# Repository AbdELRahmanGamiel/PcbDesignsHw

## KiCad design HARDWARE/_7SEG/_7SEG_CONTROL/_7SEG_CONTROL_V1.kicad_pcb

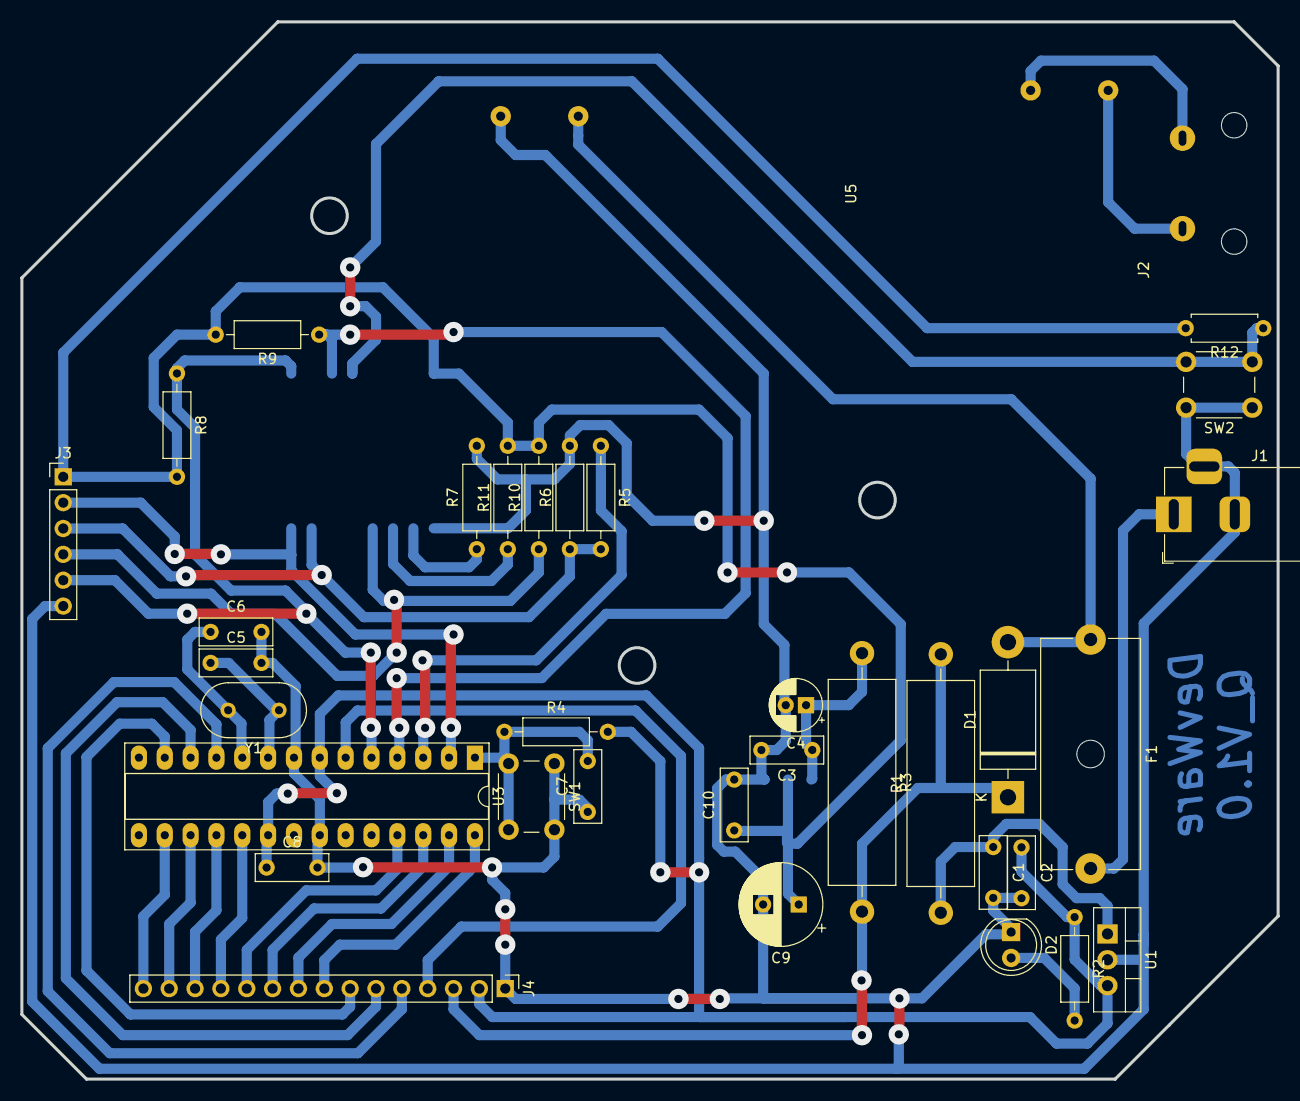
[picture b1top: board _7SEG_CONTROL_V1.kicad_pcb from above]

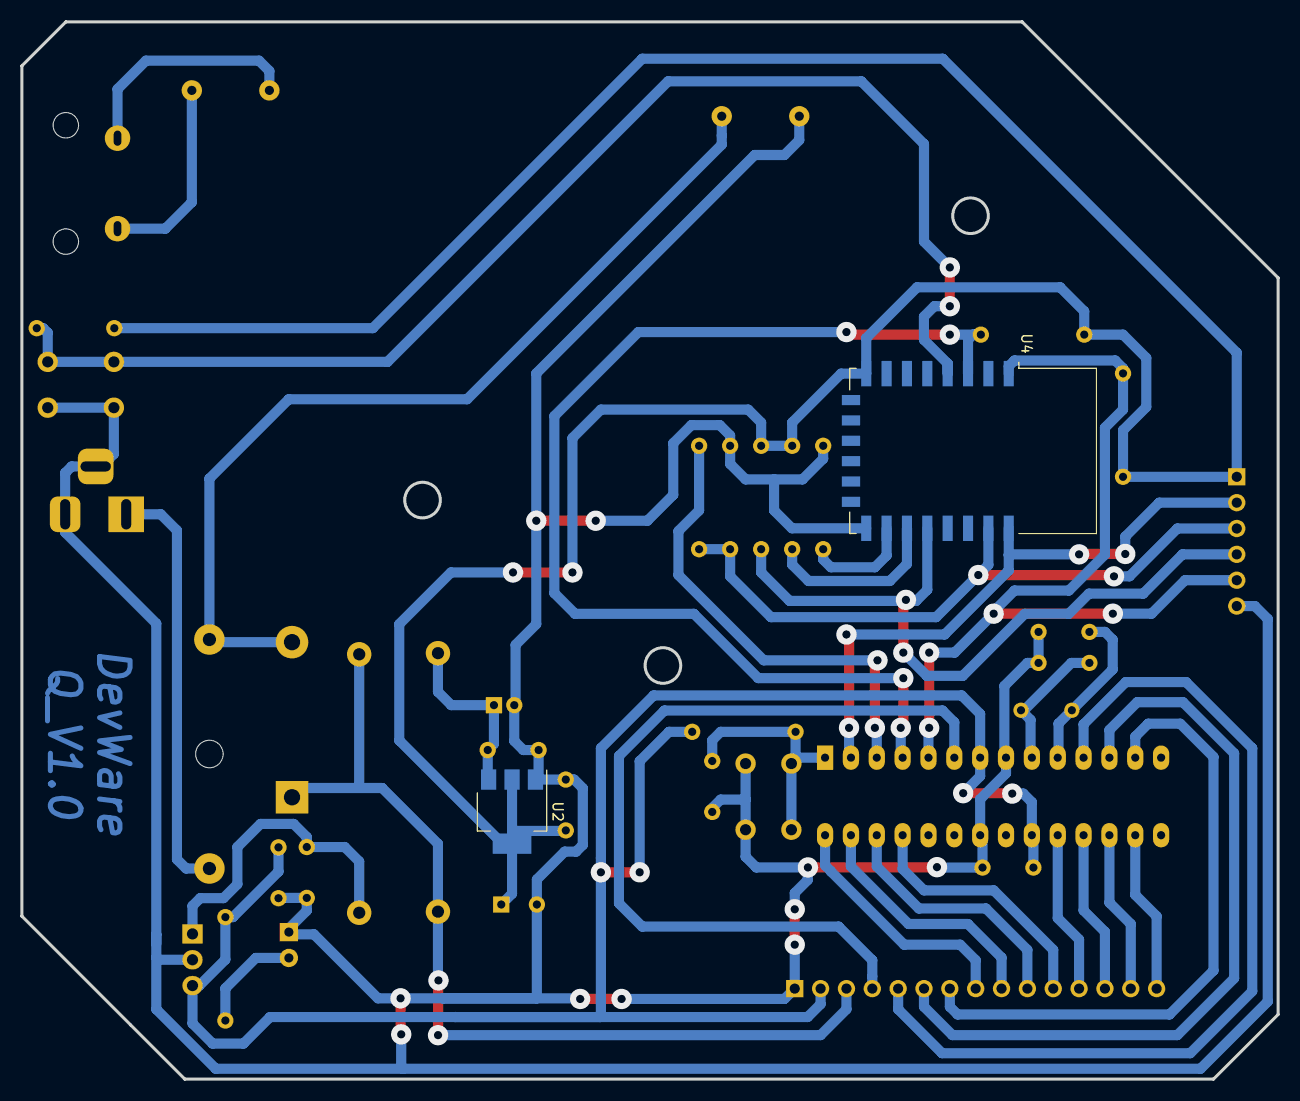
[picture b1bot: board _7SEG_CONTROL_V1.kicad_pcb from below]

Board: 2 copper layers, 123.4 x 103.9 mm, 37 parts (2 on the bottom side), 35 nets.

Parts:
C1, C3: 334; C_Disc_D7.0mm_W2.5mm_P5.00mm
C2, C7, C10: 104; C_Disc_D7.0mm_W2.5mm_P5.00mm
C4: 10UF; CP_Radial_D5.0mm_P2.00mm
C5, C6: 22P; C_Disc_D7.0mm_W2.5mm_P5.00mm
C8: 0.1UF; C_Disc_D7.0mm_W2.5mm_P5.00mm
C9: 100UF; CP_Radial_D8.0mm_P3.50mm
D1: 1N5407; D_DO-201AD_P15.24mm_Horizontal
D2: LED; LED_D5.0mm
F1: Fuse; Fuseholder_Cylinder-5x20mm_Schurter_0031_8201_Horizontal_Op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
J1: Barrel_Jack_Switch; BarrelJack_Horizontal
J2: AC_Socket
J3: CONFIG_ESP12; PinHeader_1x06_P2.54mm_Vertical
J4: Display_Board; PinHeader_1x15_P2.54mm_Vertical
R1: 10/2W; R_Axial_Power_L20.0mm_W6.4mm_P25.40mm
R2: 330; R_Axial_DIN0207_L6.3mm_D2.5mm_P10.16mm_Horizontal
R3: 10/3W; R_Axial_Power_L20.0mm_W6.4mm_P25.40mm
R4, R5, R6: 10K; R_Axial_DIN0207_L6.3mm_D2.5mm_P10.16mm_Horizontal
R7, R8, R9, R10, R11: 12K; R_Axial_DIN0207_L6.3mm_D2.5mm_P10.16mm_Horizontal
R12: 10K; R_Axial_DIN0207_L6.3mm_D2.5mm_P7.62mm_Horizontal
SW1, SW2: SW_Push; SW_PUSH_6mm_H7.3mm
U1: L7805; TO-220-3_Vertical
U2: AMS1117-3.3; SOT-223-3_TabPin2
U3: ATmega328-PU; DIP-28_W7.62mm_Socket_LongPads
U4: ESP-12E
U5: PS-12VDC; PS_12VDC
Y1: 16MH; Resonator-2Pin_W10.0mm_H5.0mm

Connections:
/3.3V: C9.1, C10.1, J3.1, R8.2, R9.2, R10.2, R11.2, R12.2, U2.2, U4.8
/5V: C2.1, C8.1, J4.2, R2.1, R4.2, U1.3, U3.7, U3.20
/12V: D1.1, J4.3, R1.2, R3.2
/A_D1: J4.15, U3.16
/A_D2: J4.11, U3.25
/A_D3: J4.7, U3.13
/B_D1: J4.12, U3.19
/B_D2: J4.8, U3.28
/B_D3: J4.4, U3.6
/C_D1: J4.13, U3.18
/C_D2: J4.9, U3.27
/C_D3: J4.5, U3.11
/D_D1: J4.14, U3.17
/D_D2: J4.10, U3.26
/D_D3: J4.6, U3.12
/EN: R9.1, U3.4, U4.3
/GND: C1.2, C2.2, C3.2, C4.2, C5.2, C6.2, C7.1, C8.2, C9.2, C10.2, D2.1, J1.2, J1.3, J3.6, J4.1, R6.2, R7.2, SW1.1, SW2.1, U1.2, U2.1, U3.8, U3.22, U4.15, U5.4
/IO0: J3.4, R10.1, U4.18
/IO2: R11.1, U4.17
/IO15: R7.1, U4.16
/Interrupt: R12.1, SW2.2, U4.4
/RST: J3.5, R8.1, U3.5, U4.1
/RX-MCU: J3.2, U3.2, U4.22
/RXD: J3.3, R5.2, R6.1, U4.21
/TX_MCU: R5.1, U3.3
/V+: D1.2, F1.1, U5.3
unnamed: C1.1, R1.1, U1.1
unnamed: C3.1, C4.1, R3.1, U2.3
unnamed: C5.1, U3.9, Y1.1
unnamed: C6.1, U3.10, Y1.2
unnamed: C7.2, R4.1, SW1.2, U3.1
unnamed: D2.2, R2.2
unnamed: F1.2, J1.1
unnamed: J2.L, U5.1
unnamed: J2.N, U5.2

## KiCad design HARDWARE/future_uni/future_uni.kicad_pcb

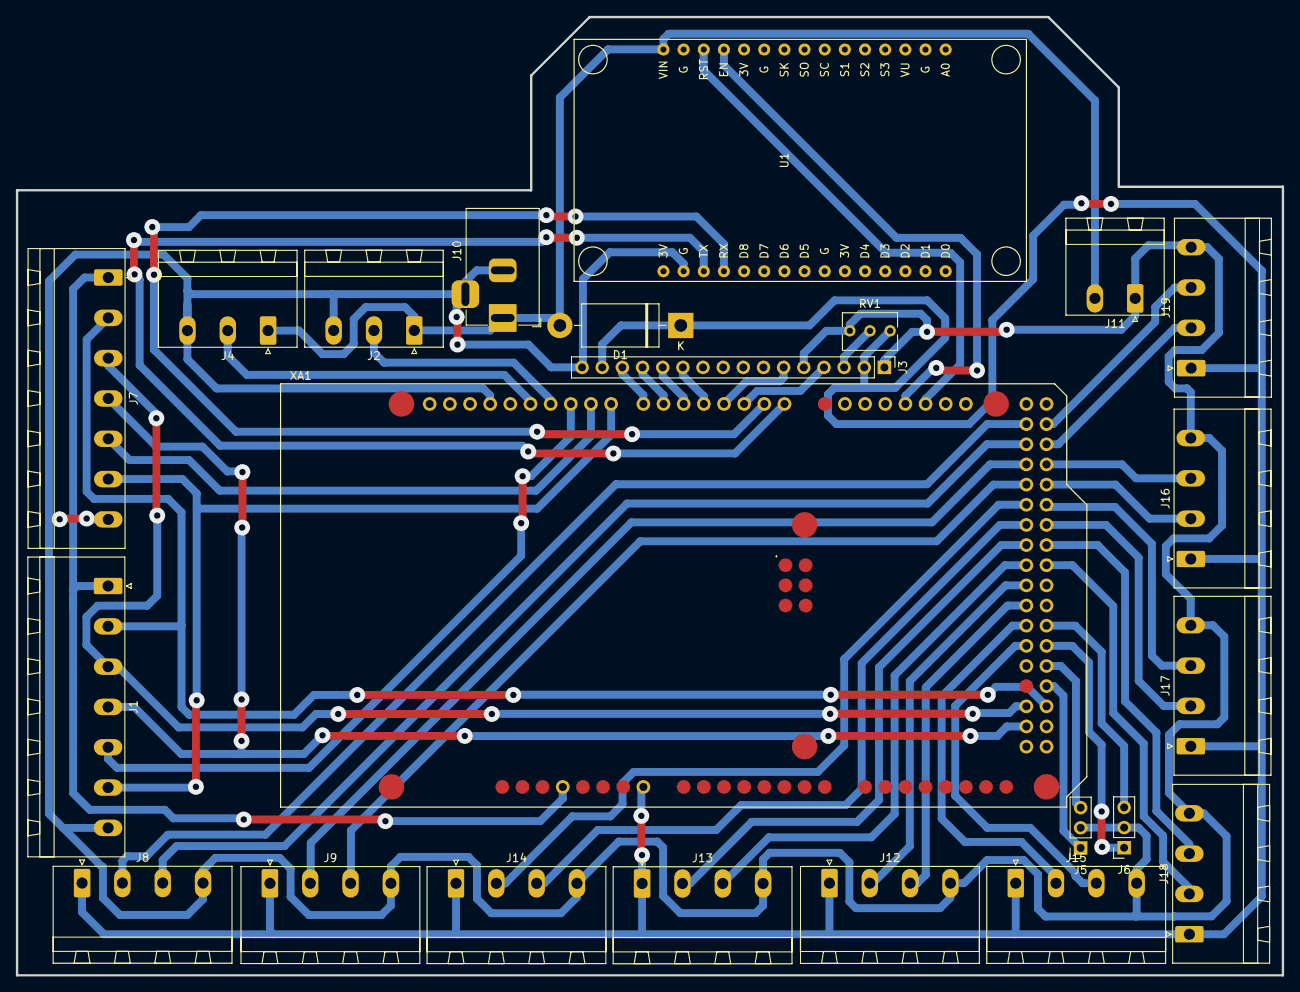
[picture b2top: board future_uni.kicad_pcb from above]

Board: 2 copper layers, 159.5 x 120.8 mm, 23 parts (0 on the bottom side), 47 nets.

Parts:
D1: D; D_DO-201AD_P15.24mm_Horizontal
J1: RFID_2; PhoenixContact_MSTBA_2,5_7-G-5,08_1x07_P5.08mm_Horizontal
J2: Servo_1; PhoenixContact_MSTBA_2,5_3-G-5,08_1x03_P5.08mm_Horizontal
J3: LCD (2*16); PinHeader_1x16_P2.54mm_Vertical
J4: Servo_2; PhoenixContact_MSTBA_2,5_3-G-5,08_1x03_P5.08mm_Horizontal
J5: RGB_1; PinSocket_1x03_P2.54mm_Vertical
J6: RGB_2; PinSocket_1x03_P2.54mm_Vertical
J7: RFID_1; PhoenixContact_MSTBA_2,5_7-G-5,08_1x07_P5.08mm_Horizontal
J8: Ultra_10; PhoenixContact_MSTBA_2,5_4-G-5,08_1x04_P5.08mm_Horizontal
J9: Ultra_9; PhoenixContact_MSTBA_2,5_4-G-5,08_1x04_P5.08mm_Horizontal
J10: 5V_PWR; BarrelJack_Horizontal
J11: 5V_PWR; PhoenixContact_MSTBA_2,5_2-G-5,08_1x02_P5.08mm_Horizontal
J12: Ultra_6; PhoenixContact_MSTBA_2,5_4-G-5,08_1x04_P5.08mm_Horizontal
J13: Ultra_7; PhoenixContact_MSTBA_2,5_4-G-5,08_1x04_P5.08mm_Horizontal
J14: Ultra_8; PhoenixContact_MSTBA_2,5_4-G-5,08_1x04_P5.08mm_Horizontal
J15: Ultra_5; PhoenixContact_MSTBA_2,5_4-G-5,08_1x04_P5.08mm_Horizontal
J16: Ultra_2; PhoenixContact_MSTBA_2,5_4-G-5,08_1x04_P5.08mm_Horizontal
J17: Ultra_3; PhoenixContact_MSTBA_2,5_4-G-5,08_1x04_P5.08mm_Horizontal
J18: Ultra_4; PhoenixContact_MSTBA_2,5_4-G-5,08_1x04_P5.08mm_Horizontal
J19: Ultra_1; PhoenixContact_MSTBA_2,5_4-G-5,08_1x04_P5.08mm_Horizontal
RV1: R_POT; Potentiometer_Bourns_3266Y_Vertical
U1: NodeMCU1.0(ESP-12E); NodeMCU-LoLinV3
XA1: Arduino_Mega2560_Shield

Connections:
/3.3V: J1.1, J7.1, XA1.3V3
/5V: D1.1, J3.2, J3.15, J8.1, J9.1, J12.1, J13.1, J14.1, J15.1, J16.1, J17.1, J18.1, J19.1, RV1.1, XA1.VIN
/DB4: J3.11, XA1.D4
/DB5: J3.12, XA1.D5
/DB6: J3.13, XA1.D6
/DB7: J3.14, XA1.D7
/E: J3.6, XA1.D3
/ECHO_1: J19.3, XA1.D23
/ECHO_2: J16.3, XA1.D27
/ECHO_3: J17.3, XA1.D31
/ECHO_4: J18.3, XA1.D35
/ECHO_5: J15.3, XA1.D44
/ECHO_6: J12.3, XA1.D40
/ECHO_7: J13.3, XA1.D36
/ECHO_8: J14.3, XA1.D32
/ECHO_9: J9.3, XA1.D28
/ECHO_10: J8.3, XA1.D24
/EN_ESP: U1.12, XA1.D18
/GND: J1.7, J2.3, J3.1, J3.5, J3.16, J4.3, J5.2, J6.2, J7.7, J8.4, J9.4, J10.2, J10.3, J11.1, J12.4, J13.4, J14.4, J15.4, J16.4, J17.4, J18.4, J19.4, RV1.3, U1.17, XA1.GND1
/GREEN_1: J5.3, XA1.D47
/GREEN_2: J6.3, XA1.D43
/MISO: J1.3, J7.3, XA1.D50
/MOSI: J1.2, J7.2, XA1.D51
/RED_1: J5.1, XA1.D49
/RED_2: J6.1, XA1.D45
/RS: J3.4, XA1.D2
/RST: J1.6, J7.6, XA1.D8
/RST_ESP: U1.13, XA1.D19
/RX_MCU: U1.18, XA1.D0
/SCK: J1.4, J7.4, XA1.D52
/SDA\SS_1: J7.5, XA1.D9
/SDA\SS_2: J1.5, XA1.D10
/Signal_1: J2.2, XA1.D11
/Signal_2: J4.2, XA1.D12
/TRIG_1: J19.2, XA1.D25
/TRIG_2: J16.2, XA1.D29
/TRIG_3: J17.2, XA1.D33
/TRIG_4: J18.2, XA1.D37
/TRIG_5: J15.2, XA1.D42
/TRIG_6: J12.2, XA1.D38
/TRIG_7: J13.2, XA1.D34
/TRIG_8: J14.2, XA1.D30
/TRIG_9: J9.2, XA1.D26
/TRIG_10: J8.2, XA1.D22
/TX_MCU: U1.19, XA1.D1
/VIN: D1.2, J2.1, J4.1, J10.1, J11.2, U1.15
/VO: J3.3, RV1.2

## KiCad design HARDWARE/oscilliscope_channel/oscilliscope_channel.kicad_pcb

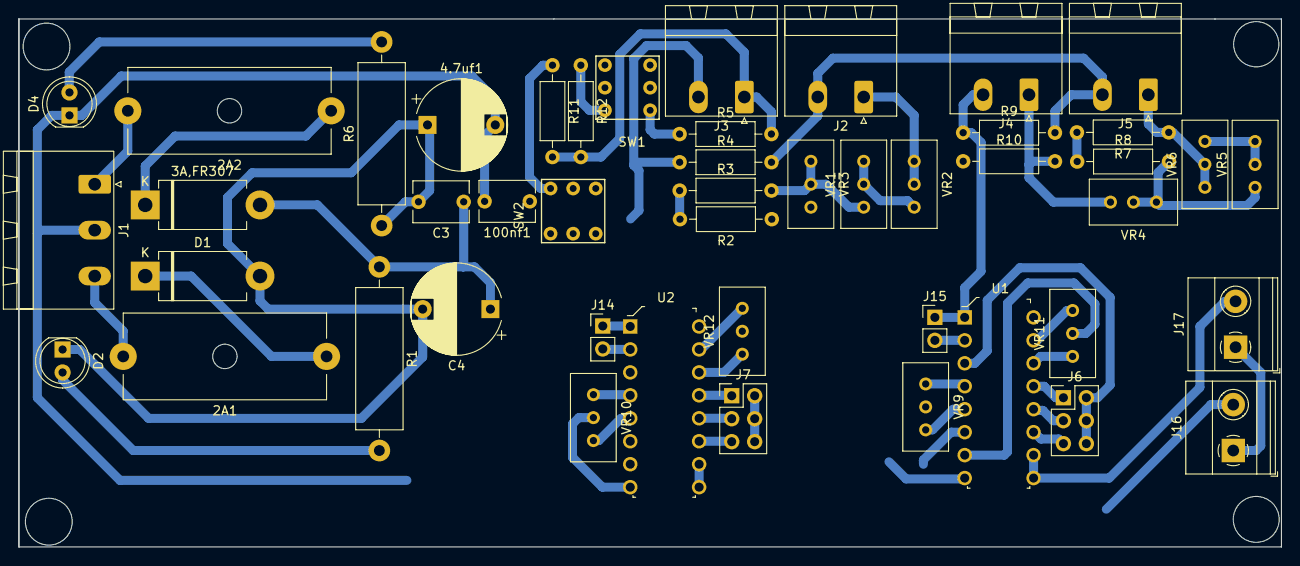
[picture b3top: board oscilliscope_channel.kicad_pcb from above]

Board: 2 copper layers, 139.7 x 58.4 mm, 47 parts (0 on the bottom side), 40 nets.

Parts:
2A1, 2A2: Fuse; Fuseholder_Cylinder-5x20mm_Schurter_0031_8201_Horizontal_Op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
3A,FR307: DIODE; D_DO-201AD_P12.70mm_Horizontal
4.7uf1: CP; CP_Radial_D10.0mm_P7.50mm
100nf1: C; C_Disc_D6.0mm_W4.4mm_P5.00mm
C3: 100nf; C_Disc_D6.0mm_W4.4mm_P5.00mm
C4: 4.7uf,25v; CP_Radial_D10.0mm_P7.50mm
D1: 3A,FR307; D_DO-201AD_P12.70mm_Horizontal
D2, D4: LED; LED_D5.0mm
J1: Screw_Terminal_01x03; PhoenixContact_MSTBA_2,5_3-G-5,08_1x03_P5.08mm_Horizontal
J2, J3, J4, J5: Screw_Terminal_01x02; PhoenixContact_MSTBA_2,5_2-G-5,08_1x02_P5.08mm_Horizontal
J6, J7: Conn_02x03_Counter_Clockwise; PinHeader_2x03_P2.54mm_Vertical
J14, J15: Conn_01x02_Male; PinHeader_1x02_P2.54mm_Vertical
J16, J17: Screw_Terminal_01x02; TerminalBlock_Phoenix_MKDS-1,5-2-5.08_1x02_P5.08mm_Horizont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
R1: 910OHM,1W; R_Axial_DIN0516_L15.5mm_D5.0mm_P20.32mm_Horizontal
R2, R7: 10kohm; R_Axial_DIN0207_L6.3mm_D2.5mm_P10.16mm_Horizontal
R3, R8: 1kohm; R_Axial_DIN0207_L6.3mm_D2.5mm_P10.16mm_Horizontal
R4, R9: 120ohm; R_Axial_DIN0207_L6.3mm_D2.5mm_P10.16mm_Horizontal
R5, R10: 150ohm; R_Axial_DIN0207_L6.3mm_D2.5mm_P10.16mm_Horizontal
R6: 910ohm,1W; R_Axial_DIN0516_L15.5mm_D5.0mm_P20.32mm_Horizontal
R11, R12: 20kohm; R_Axial_DIN0207_L6.3mm_D2.5mm_P10.16mm_Horizontal
SW1, SW2: SW_DIP_x03
U1, U2: AD524BDZ; DIP-16_W7.62mm
VR1, VR5: 1KOHM; Potentiometer_Bourns_3296W_Vertical
VR2, VR6: 5KOHM; Potentiometer_Bourns_3296W_Vertical
VR3, VR4: 500OHM; Potentiometer_Bourns_3296W_Vertical
VR9, VR10, VR11, VR12: 10KOHM; Potentiometer_Bourns_3296W_Vertical

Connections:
/5V: J3.1, J4.1, R5.2, R10.2, R11.2, R12.2, VR3.1, VR4.1
/15V: 3A,FR307.2, C3.1, C4.1, R1.1, U1.8, U2.8, VR9.2, VR10.2
/-15V: 4.7uf1.2, 100nf1.2, D4.1, J1.2, U1.7, U2.7, VR11.2, VR12.2
/G10-1: J7.1, U2.13
/G10-2: J6.1, U1.13
/G100-1: J7.3, U2.12
/G100-2: J6.3, U1.12
/G1000-1: J7.5, U2.11
/G1000-2: J6.5, U1.11
/GND: 4.7uf1.1, 100nf1.1, C3.2, C4.2, D1.2, D2.1, J2.2, J5.2, J16.1, J17.1, R4.2, R6.1, R9.2, U1.6, U2.6
/OUT1: J16.2, U2.9, U2.10
/OUT-2: J17.2, U1.9, U1.10
/P1-1: J3.2, J14.1, R4.1, U2.1
/P1-2: J2.1, J14.2, R2.1, R5.1, SW1.1, U2.2, VR2.2, VR2.3
/P2-1: J4.2, J15.1, R9.1, U1.1
/P2-2: J5.1, J15.2, R7.1, R10.1, SW2.1, U1.2, VR6.2, VR6.3
/RG2-1: J7.2, J7.4, J7.6, U2.3
/RG2-2: J6.2, J6.4, J6.6, U1.3
unnamed: 2A1.1, D1.1
unnamed: 2A1.2, J1.3
unnamed: 2A2.1, 3A,FR307.1
unnamed: 2A2.2, J1.1
unnamed: D2.2, R1.2
unnamed: D4.2, R6.2
unnamed: R2.2, R3.1
unnamed: R3.2, VR1.3, VR3.2, VR3.3
unnamed: R7.2, R8.1
unnamed: R8.2, VR4.2, VR4.3, VR5.3
unnamed: R11.1, SW2.2
unnamed: R12.1, SW1.2
unnamed: U1.4, VR9.3
unnamed: U1.5, VR9.1
unnamed: U1.14, VR11.3
unnamed: U1.15, VR11.1
unnamed: U2.4, VR10.3
unnamed: U2.5, VR10.1
unnamed: U2.14, VR12.3
unnamed: U2.15, VR12.1
unnamed: VR1.1, VR1.2, VR2.1
unnamed: VR5.1, VR5.2, VR6.1

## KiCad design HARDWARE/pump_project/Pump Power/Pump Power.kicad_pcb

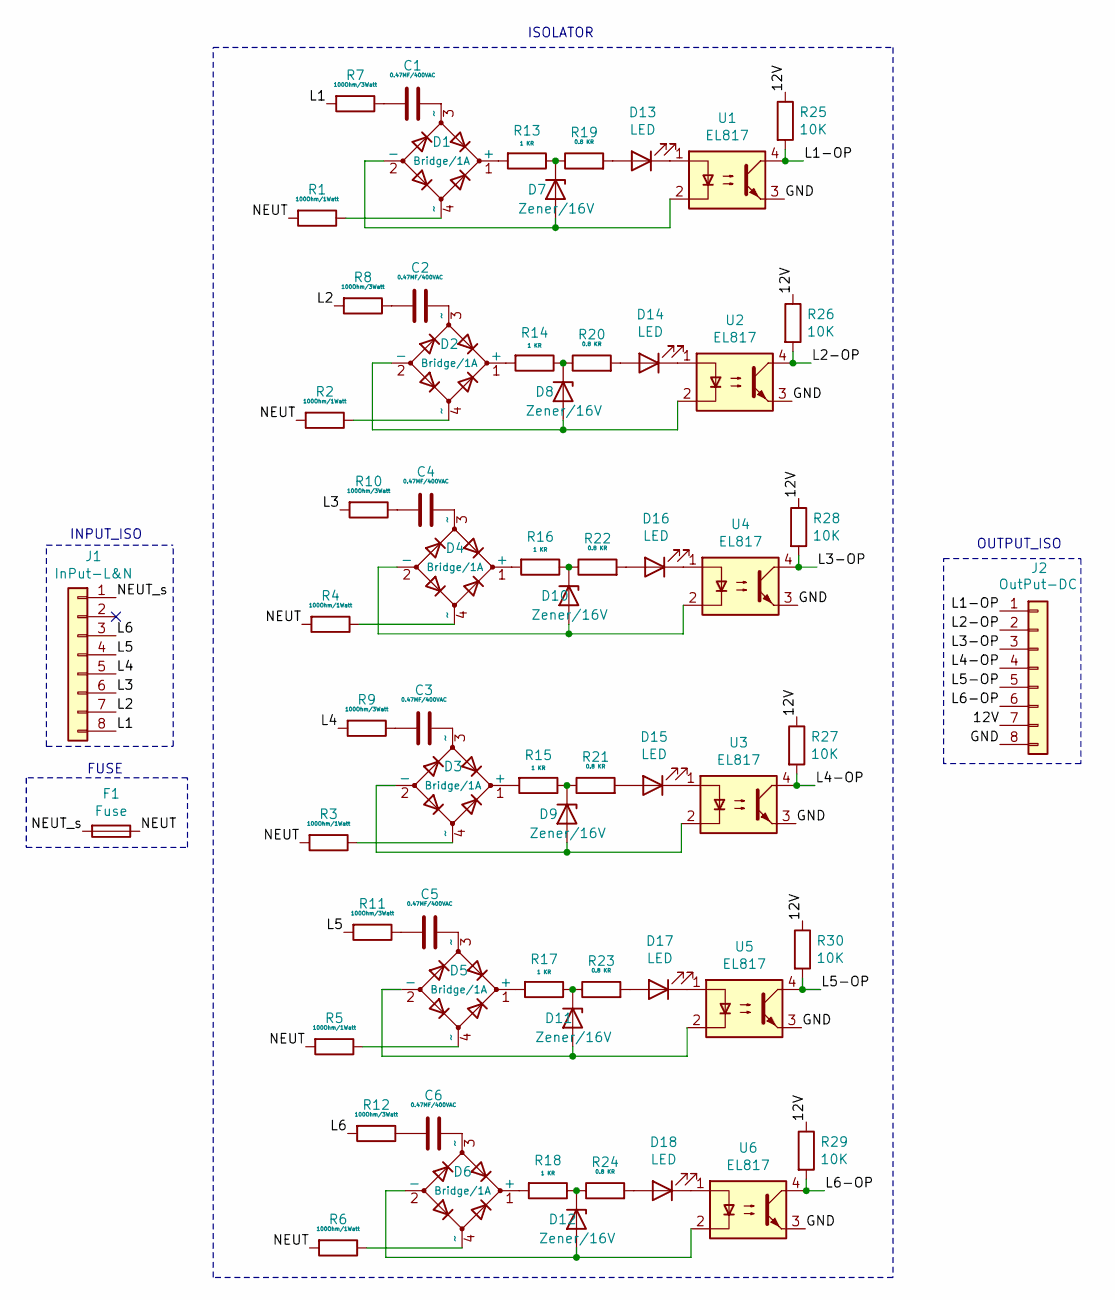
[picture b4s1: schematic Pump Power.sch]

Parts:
C1, C2, C3, C4, C5, C6: 0.47MF/400VAC; C_Rect_L11.5mm_W5.6mm_P10.00mm_MKT
D1, D2, D3, D4, D5, D6: Bridge/1A; Diode_Bridge_Round_D9.8mm
D7, D8, D9, D10, D11, D12: Zener/16V; D_A-405_P7.62mm_Horizontal
D13, D14, D15, D16, D17, D18: LED; LED_D5.0mm
F1: Fuse; Fuseholder_Cylinder-6.3x32mm_Schurter_0031-8002_Horizontal_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
J1: InPut-L&N; PhoenixContact_MSTBA_2,5_8-G-5,08_1x08_P5.08mm_Horizontal
J2: OutPut-DC; PhoenixContact_MSTBA_2,5_8-G-5,08_1x08_P5.08mm_Horizontal
R1, R2, R3, R4, R5, R6: 100Ohm/1Watt; R_Axial_DIN0617_L17.0mm_D6.0mm_P20.32mm_Horizontal
R7, R8, R9, R10, R11, R12: 100Ohm/3Watt; R_Axial_Power_L25.0mm_W9.0mm_P27.94mm
R13, R14, R15, R16, R17, R18: 1 KR; R_Axial_DIN0207_L6.3mm_D2.5mm_P10.16mm_Horizontal
R19, R20, R21, R22, R23, R24: 0.8 KR; R_Axial_DIN0207_L6.3mm_D2.5mm_P10.16mm_Horizontal
R25, R26, R27, R28, R29, R30: 10K; R_Axial_DIN0207_L6.3mm_D2.5mm_P10.16mm_Horizontal
U1, U2, U3, U4, U5, U6: EL817; DIP-4_W7.62mm

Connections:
/12V: J2.7, R25.1, R26.1, R27.1, R28.1, R29.1, R30.1
/GND: J2.8, U1.3, U2.3, U3.3, U4.3, U5.3, U6.3
/L1: J1.8, R7.2
/L1-OP: J2.1, R25.2, U1.4
/L2: J1.7, R8.2
/L2-OP: J2.2, R26.2, U2.4
/L3: J1.6, R10.2
/L3-OP: J2.3, R28.2, U4.4
/L4: J1.5, R9.2
/L4-OP: J2.4, R27.2, U3.4
/L5: J1.4, R11.2
/L5-OP: J2.5, R30.2, U5.4
/L6: J1.3, R12.2
/L6-OP: J2.6, R29.2, U6.4
/NEUT: F1.1, R1.2, R2.2, R3.2, R4.2, R5.2, R6.2
/NEUT_s: F1.2, J1.1
unnamed: C1.1, D1.3 (~~)
unnamed: C1.2, R7.1
unnamed: C2.1, D2.3 (~~)
unnamed: C2.2, R8.1
unnamed: C3.1, D3.3 (~~)
unnamed: C3.2, R9.1
unnamed: C4.1, D4.3 (~~)
unnamed: C4.2, R10.1
unnamed: C5.1, D5.3 (~~)
unnamed: C5.2, R11.1
unnamed: C6.1, D6.3 (~~)
unnamed: C6.2, R12.1
unnamed: D1.1 (+), R13.2
unnamed: D1.2 (-), D7.2 (A), U1.2
unnamed: D1.4 (~~), R1.1
unnamed: D2.1 (+), R14.2
unnamed: D2.2 (-), D8.2 (A), U2.2
unnamed: D2.4 (~~), R2.1
unnamed: D3.1 (+), R15.2
unnamed: D3.2 (-), D9.2 (A), U3.2
unnamed: D3.4 (~~), R3.1
unnamed: D4.1 (+), R16.2
unnamed: D4.4 (~~), R4.1
unnamed: D5.1 (+), R17.2
unnamed: D5.4 (~~), R5.1
unnamed: D6.1 (+), R18.2
unnamed: D6.4 (~~), R6.1
unnamed: D7.1 (K), R13.1, R19.1
unnamed: D8.1 (K), R14.1, R20.1
unnamed: D9.1 (K), R15.1, R21.1
unnamed: D10.1 (K), R16.1, R22.1
unnamed: D4.2 (-), D10.2 (A), U4.2
unnamed: D11.1 (K), R17.1, R23.1
unnamed: D5.2 (-), D11.2 (A), U5.2
unnamed: D12.1 (K), R18.1, R24.1
unnamed: D6.2 (-), D12.2 (A), U6.2
unnamed: D13.1 (K), U1.1
unnamed: D13.2 (A), R19.2
unnamed: D14.1 (K), U2.1
unnamed: D14.2 (A), R20.2
unnamed: D15.1 (K), U3.1
unnamed: D15.2 (A), R21.2
unnamed: D16.1 (K), U4.1
unnamed: D16.2 (A), R22.2
unnamed: D17.1 (K), U5.1
unnamed: D17.2 (A), R23.2
unnamed: D18.1 (K), U6.1
unnamed: D18.2 (A), R24.2

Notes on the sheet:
ISOLATOR
INPUT_ISO
OUTPUT_ISO
FUSE

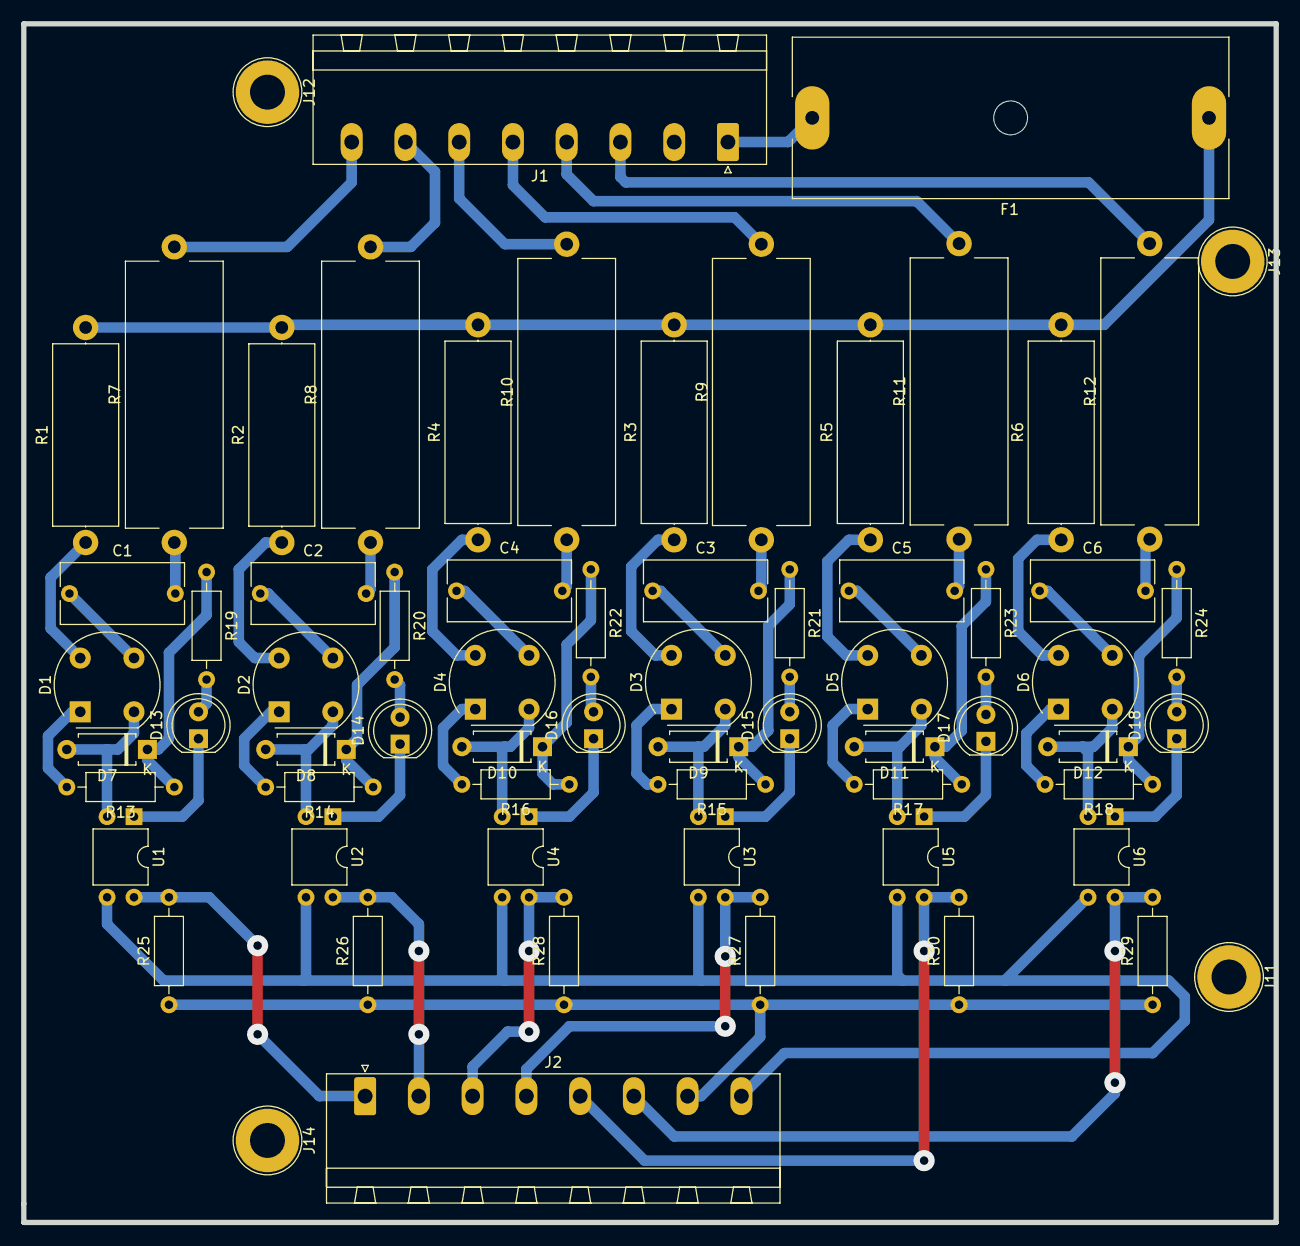
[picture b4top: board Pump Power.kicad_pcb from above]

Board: 2 copper layers, 118.4 x 113.3 mm, 67 parts (0 on the bottom side), 64 nets.

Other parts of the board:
J11, J12, J13, J14: Screw_Terminal_01x01; TestPoint_Plated_Hole_D5.0mm

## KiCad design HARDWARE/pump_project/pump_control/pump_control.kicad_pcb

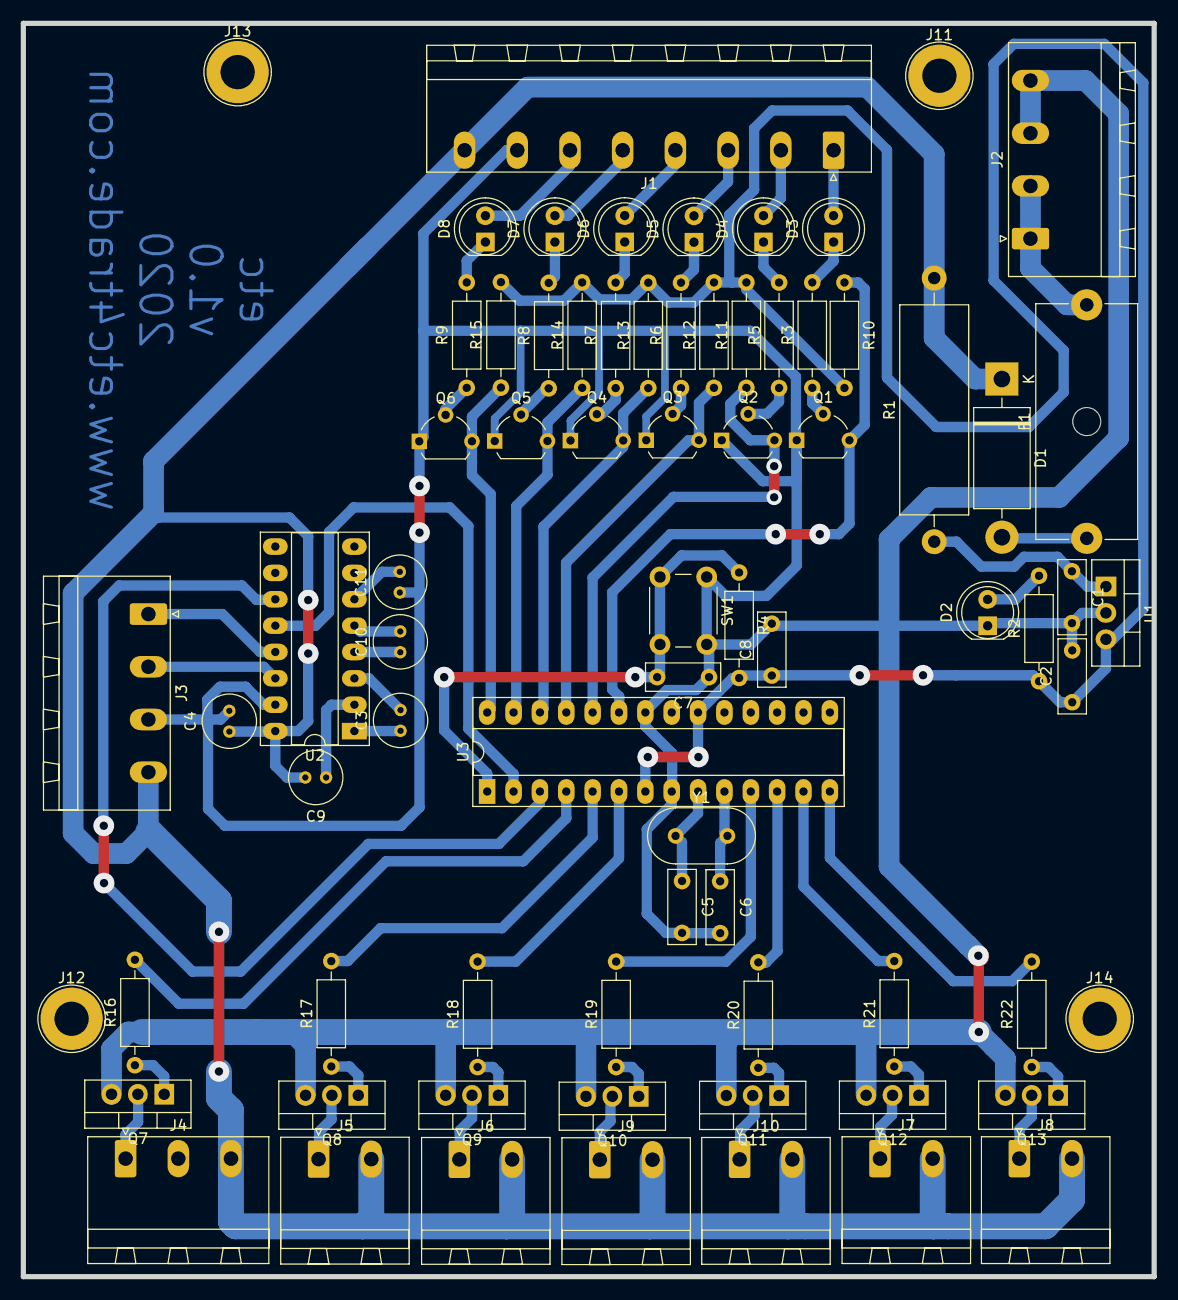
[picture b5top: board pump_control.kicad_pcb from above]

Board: 2 copper layers, 109.0 x 120.8 mm, 74 parts (0 on the bottom side), 65 nets.

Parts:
C1: 334; C_Disc_D7.0mm_W2.5mm_P5.00mm
C2, C7: 104; C_Disc_D7.0mm_W2.5mm_P5.00mm
C3, C4, C9, C10, C11: 1uF; C_Radial_D5.0mm_H5.0mm_P2.00mm
C5, C6: 22P; C_Disc_D7.0mm_W2.5mm_P5.00mm
C8: 0.1UF; C_Disc_D7.0mm_W2.5mm_P5.00mm
D1: 1N5407; D_DO-201AD_P15.24mm_Horizontal
D2, D3, D4, D5, D6, D7, D8: LED; LED_D5.0mm
F1: Fuse; Fuseholder_Cylinder-5x20mm_Schurter_0031_8201_Horizontal_Op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
J1: input_signal; PhoenixContact_MSTBA_2,5_8-G-5,08_1x08_P5.08mm_Horizontal
J2: INPUT_PWR; PhoenixContact_MSTBA_2,5_4-G-5,08_1x04_P5.08mm_Horizontal
J3: TO_USER_INTER; PhoenixContact_MSTBA_2,5_4-G-5,08_1x04_P5.08mm_Horizontal
J4: Valve; PhoenixContact_MSTBA_2,5_3-G-5,08_1x03_P5.08mm_Horizontal
J5: P6; PhoenixContact_MSTBA_2,5_2-G-5,08_1x02_P5.08mm_Horizontal
J6: P5; PhoenixContact_MSTBA_2,5_2-G-5,08_1x02_P5.08mm_Horizontal
J7: P2; PhoenixContact_MSTBA_2,5_2-G-5,08_1x02_P5.08mm_Horizontal
J8: P1; PhoenixContact_MSTBA_2,5_2-G-5,08_1x02_P5.08mm_Horizontal
J9: P4; PhoenixContact_MSTBA_2,5_2-G-5,08_1x02_P5.08mm_Horizontal
J10: P3; PhoenixContact_MSTBA_2,5_2-G-5,08_1x02_P5.08mm_Horizontal
J11, J12, J13, J14: Screw_Terminal_01x01; TestPoint_Plated_Hole_D5.0mm
Q1, Q2, Q3, Q4, Q5, Q6: 2N2219; TO-92L_Wide
Q7, Q8, Q9, Q10, Q11, Q12, Q13: TIP41; TO-220-3_Vertical
R1: 10/2W; R_Axial_Power_L20.0mm_W6.4mm_P25.40mm
R2: 330; R_Axial_DIN0207_L6.3mm_D2.5mm_P10.16mm_Horizontal
R3, R5, R6, R7, R8, R9: 2K; R_Axial_DIN0207_L6.3mm_D2.5mm_P10.16mm_Horizontal
R4, R10, R11, R12, R13, R14, R15: 10K; R_Axial_DIN0207_L6.3mm_D2.5mm_P10.16mm_Horizontal
R16, R17, R18, R19, R20, R21, R22: 1K; R_Axial_DIN0207_L6.3mm_D2.5mm_P10.16mm_Horizontal
SW1: SW_Push; SW_PUSH_6mm_H7.3mm
U1: L7805; TO-220-3_Vertical
U2: MAX232; DIP-16_W7.62mm_Socket_LongPads
U3: ATmega328-PU; DIP-28_W7.62mm_Socket_LongPads
Y1: 16MH; Resonator-2Pin_W10.0mm_H5.0mm

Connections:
+5V: C2.1, C8.1, R2.1, R4.2, R10.2, R11.2, R12.2, R13.2, R14.2, R15.2, U1.3, U3.7, U3.20
+12V: C4.1, C9.2, D1.1, J1.8, J3.4, J4.3, J5.2, J6.2, J7.2, J8.2, J9.2, J10.2, R1.2, U2.16
/IN_S_1: Q1.3, R10.1, U3.23
/IN_S_2: Q2.3, R11.1, U3.24
/IN_S_3: Q3.3, R12.1, U3.25
/IN_S_4: Q4.3, R13.1, U3.26
/IN_S_5: Q5.3, R14.1, U3.27
/IN_S_6: Q6.3, R15.1, U3.28
/OUT_P1: J8.1, Q13.2
/OUT_P2: J7.1, Q12.2
/OUT_P3: J10.1, Q11.2
/OUT_P4: J9.1, Q10.2
/OUT_P5: J6.1, Q9.2
/OUT_P6: J5.1, Q8.2
/P1_MCU: R22.2, U3.14
/P2_MCU: R21.2, U3.13
/P3_MCU: R20.2, U3.12
/P4_MCU: R19.2, U3.11
/P5_MCU: R18.2, U3.6
/P6_MCU: R17.2, U3.5
/RX: U2.12, U3.2
/RX_T: J3.1, U2.13
/S1: D3.2, J1.1
/S2: D4.2, J1.2
/S3: D5.2, J1.3
/S4: D6.2, J1.4
/S5: D7.2, J1.5
/S6: D8.2, J1.6
/TX: U2.11, U3.3
/TX_T: J3.2, U2.14
/Valve: J4.1, Q7.2
/Valve_MCU: R16.2, U3.4
/v_ip: F1.2, J2.1, J2.2
GND: C1.2, C2.2, C4.2, C5.2, C6.2, C7.1, C8.2, C11.1, D2.1, J1.7, J2.3, J2.4, J3.3, Q1.1, Q2.1, Q3.1, Q4.1, Q5.1, Q6.1, Q7.3, Q8.3, Q9.3, Q10.3, Q11.3, Q12.3, Q13.3, SW1.1, U1.2, U2.15, U3.8, U3.22
unnamed: C1.1, R1.1, U1.1
unnamed: C3.1, U2.1
unnamed: C3.2, U2.3
unnamed: C5.1, U3.9, Y1.1
unnamed: C6.1, U3.10, Y1.2
unnamed: C7.2, R4.1, SW1.2, U3.1
unnamed: C9.1, U2.2
unnamed: C10.1, U2.4
unnamed: C10.2, U2.5
unnamed: C11.2, U2.6
unnamed: D1.2, F1.1
unnamed: D2.2, R2.2
unnamed: D3.1, R3.2
unnamed: D4.1, R5.2
unnamed: D5.1, R6.2
unnamed: D6.1, R7.2
unnamed: D7.1, R8.2
unnamed: D8.1, R9.2
unnamed: Q1.2, R3.1
unnamed: Q2.2, R5.1
unnamed: Q3.2, R6.1
unnamed: Q4.2, R7.1
unnamed: Q5.2, R8.1
unnamed: Q6.2, R9.1
unnamed: Q7.1, R16.1
unnamed: Q8.1, R17.1
unnamed: Q9.1, R18.1
unnamed: Q10.1, R19.1
unnamed: Q11.1, R20.1
unnamed: Q12.1, R21.1
unnamed: Q13.1, R22.1
